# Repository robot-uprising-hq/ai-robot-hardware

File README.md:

# Micro Invaders - Hardware

This repository contains the hardware-related files of Robot Uprising Micro Invaders. The folder structure is as follows
* Root: Contains 3D printable basic robot parts
	* Accessories: Contains 3D printable accessories designed by Robot Uprising
	* Advanced: Contains design files
	* Images: Contains images mainly for README files
	* Misc: Contains miscellaneous 3D printable files related to the design, but not needed for the competition

The Micro Invaders robot is designed with simplicity in mind. It has very little amount of mechanical parts, and all the parts are 3D-printable. Moreover, it is designed to be assembled or disassembled without using any tools. 

If you need a 3D-printing guide, here is our guide: [3D-Printing Guide - Ultimaker 3](https://docs.google.com/document/d/1BAfrNYozn9PcpJIatZrwz-if5QTi_UQTAYi0SMTYilM/).

## Table of Contents <!-- omit in toc -->

- [Micro Invaders - Hardware](#micro-invaders---hardware)
	- [Mechanical parts](#mechanical-parts)
		- [Printing Checklist](#printing-checklist)
		- [Accesories](#accesories)
	- [Electronics](#electronics)
		- [Driver PCBA](#driver-pcba)
			- [PCB Gerber files and Bill of Materials](#pcb-gerber-files-and-bill-of-materials)
			- [PCBA Bill of Materials](#pcba-bill-of-materials)
		- [ESP32](#esp32)
		- [Motors](#motors)
		- [Batteries](#batteries)
		- [Cables and connectors](#cables-and-connectors)

## Mechanical parts

**Drive wheel:** This part drives the track, and the robot hence the name "drive wheel". The clearances are adjusted so that it fits nicely on the motor shaft, but it features a screw hole in case it doesn't.

**Idler:** This is the non-driving wheel for the tracks, but it also doubles as a tensioner. Thanks to its eccentric shaft, it can be used to adjust the slack on the chain.

**Idler retainer:** Idler retainer retains the idler :)

**Body:** This is the chassis of the robot. It houses all the parts. There are two versions of body. One is accessorizable and the other one is plain (located in Misc folder). As the name implies, accessorizable body is designed to fit accessories utilizing standard accessory connector.

**Top cover:** This part basically prevents things from falling off. It keeps the batteries in place, it prevents circuit board to fall off, and it even acts as the idler retainer retainer. All these functions in one single part. It attaches to the body by one rigid attachment point in the back, and one flexible attachment point in the front. This part also has two versions, accessorizable and plain (located in Misc folder).

**Track:** This is the part that moves the robot. It is basically a chain with 20 links.

### Printing Checklist

You will need to print the following parts for the competition.

| Amount | Part                       |
| :----: | -------------------------- |
|   1    | Body (accessorizable)      |
|   1    | Top cover (accessorizable) |
|   1    | Aruco marker holder        |
|   2    | Drive wheel                |
|   2    | Idler retainer             |
|   2    | Track                      |
|   2    | Idler                      |

See folders [Mechanics/Robot/STL](Mechanics/Robot/STL) and [Mechanics/Accessories/STL](Mechanics/Accessories/STL) for the STL-files for printing.

We recommend printing the parts in the given order as the latter parts are more advanced, and you might benefit from the experience. 
 
Also, feel free to design and print your own super exotic accessories or custom robot bodies for showing off between the matches, although you might not be allowed to use them in the competition. 

### Accesories

You can design and print your own front accessory as long as it complies with the [rules](https://github.com/robot-uprising-hq/ai-rules-mi2020).

## Electronics

### Driver PCBA

#### PCB Gerber files and Bill of Materials

You can find Gerber files for the PCB in the folder [Gerber Files](Electronics/Gerber%20Files). You can upload the compressed file to a PCB manufacturers website (e.g. JLCPCB)

Connect the right motor to J2 and the left motor to J3. Ensure motors have the correct polarity before fully assembling the robot to avoid unnecessary disassembly.

#### PCBA Bill of Materials

ID matches the schema and the PCB silkscreen

|         ID         | Description with link                                                                                                                                                                                              | Amount |
| :----------------: | ------------------------------------------------------------------------------------------------------------------------------------------------------------------------------------------------------------------ | :----: |
|       C1, C2       | [25V 100uF electrolytic THT capacitor](https://www.digikey.fi/en/products/detail/panasonic-electronic-components/ECA-1EM101B/268461)                                                                               |   2    |
|   D1, D2, D3, D4   | [RED clear 0805 SMD LED](https://www.digikey.fi/en/products/detail/liteon/LTST-C171KRKT/386801)                                                                                                                    |   4    |
|         F1         | [2.5A (Max Hold Current), 5A (Trip Current) 16V Fuse 2920 (7351 metric) package](https://www.digikey.fi/en/products/detail/bel-fuse-inc/0ZCF0250FF2C/4156185)                                                      |   1    |
|         J1         | [3-pin JST XH 2.50mm pitch connector](https://www.digikey.fi/en/products/detail/jst-sales-america-inc/S3B-XH-A/1651048)                                                                                            |   1    |
|       J2, J3       | [2-pin JST PH 2.00mm pitch connector](https://www.digikey.fi/fi/products/detail/jst-sales-america-inc/S2B-PH-SM4-TB/926655?s=N4IgTCBcDaIMpgEIFoAKAJZcCyAWZAKoiALoC%2BQA)                                           |   2    |
| R1, R2, R3, R4, R6 | [1 kΩ 0805 SMD resistor](https://www.digikey.fi/en/products/detail/stackpole-electronics-inc/RMCF0805JT1K00/1757881)                                                                                               |   5    |
|         R5         | [2.2 kΩ 0805 SMD resistor](https://www.digikey.fi/en/products/detail/stackpole-electronics-inc/RMCF0805JT2K20/1757894)                                                                                             |   1    |
|        SW1         | [Slide switch](https://www.digikey.fi/en/products/detail/c-k/OS102011MA1QN1/1981430)                                                                                                                               |   1    |
|         U1         | [7805 5V linear regulator (D2PAK Package)](https://www.digikey.fi/en/products/detail/onsemi/MC7805CD2TR4G/919332)                                                                                                  |   1    |
|    U2 (J4, J5)     | [For ESP-32 two 20-pin 2.54mm pitch female headers which needs to be trimmed to 19 pins](https://www.digikey.fi/fi/products/detail/w%C3%BCrth-elektronik/61302011821/16608603?s=N4IgTCBcDaIGwEYDMAGMKEIBxgSAugL5A) |   2    |
|         U3         | [Dual H-bridge motor driver 293D](https://www.digikey.fi/en/products/detail/stmicroelectronics/L293D/634700)                                                                                                       |   1    |

### ESP32

ESP32-DEVKITC-32E:

- 1 x https://www.digikey.fi/en/products/detail/espressif-systems/ESP32-DEVKITC-32E/12091810

### Motors

Olimex LTD: MG-6-48

- 2 x https://www.digikey.fi/en/products/detail/olimex-ltd/MG-6-48/21662315

### Batteries

Two 18650 Li-Ion batteries (we recommend >2200mAh, with protection circuit):

- 2 x https://akkula.fi/tuote/xtar-18650-li-ion-akku-2600-mah-36v-suojapiiri-button-top/

Li-Ion 18650 battery charger:

- 1 x https://akkula.fi/tuote/xtar-mc2-plus-usb-pikalaturi-kahdelle-li-ion-akulle/

18650 battery holder for two batteries:

- 1 x https://akkula.fi/tuote/2-x-18650-asennuskotelo-johdoilla-max-1-a-virta/

### Cables and connectors

We recommend getting JST XH (2.50mm pitch) and PH (2.00mm pitch) connector assortment with crimp tool.
The JST connectors require crimping the cable ends with a tool such as https://www.partco.fi/fi/tyoekalut/puristuspihdit/loput-puristuspihdit/11353-ht213.html. 
Unless you're very much into crimping all the things, instead of buying the tool you can probably find one at your local university electronics lab, makerspace or https://hacklab.fi.

There are also preassembed wires: (we recommend 12" ones so that they are long enough)

XH:
https://www.digikey.fi/en/products/filter/jumper-wires-pre-crimped-leads/453?s=N4IgTCBcDaIFYGcAuACAHgCxAXQL5A

12" ones:
https://www.digikey.fi/en/products/detail/jst-sales-america-inc/ASXHSXH22K305/6684932

PH:
https://www.digikey.fi/en/products/filter/jumper-wires-pre-crimped-leads/453?s=N4IgTCBcDaIFYGcAuACADgCxAXQL5A

12" ones:
https://www.digikey.fi/en/products/detail/jst-sales-america-inc/ASPHSPH24K305/6009459

3-pin JST XH 2.50mm pitch Connector for battery terminal:
- Female 1 x https://www.digikey.fi/fi/products/detail/jst-sales-america-inc/XHP-2/555485

2-pin JST PH 2.00mm pitch Connector for motor terminals:
- Female 2 x https://www.digikey.fi/en/products/detail/jst-sales-america-inc/PHR-2/608607

### Firmware

There are two firmware repositories for this robot.
- Control the robot using a computer: [github.com/robot-uprising-hq/ai-robot-udp](https://github.com/robot-uprising-hq/ai-robot-udp)
	- Official firmware for receiving commands over WIFI (using UDP) and limited support for bluetooth
- Control the robot using a gamepad: [github.com/zero-ones-given/bluetooth-gamepad-robot-firmware](https://github.com/zero-ones-given/bluetooth-gamepad-robot-firmware)
	- Community built firmware for controlling the robot over bluetooth with a gamepad

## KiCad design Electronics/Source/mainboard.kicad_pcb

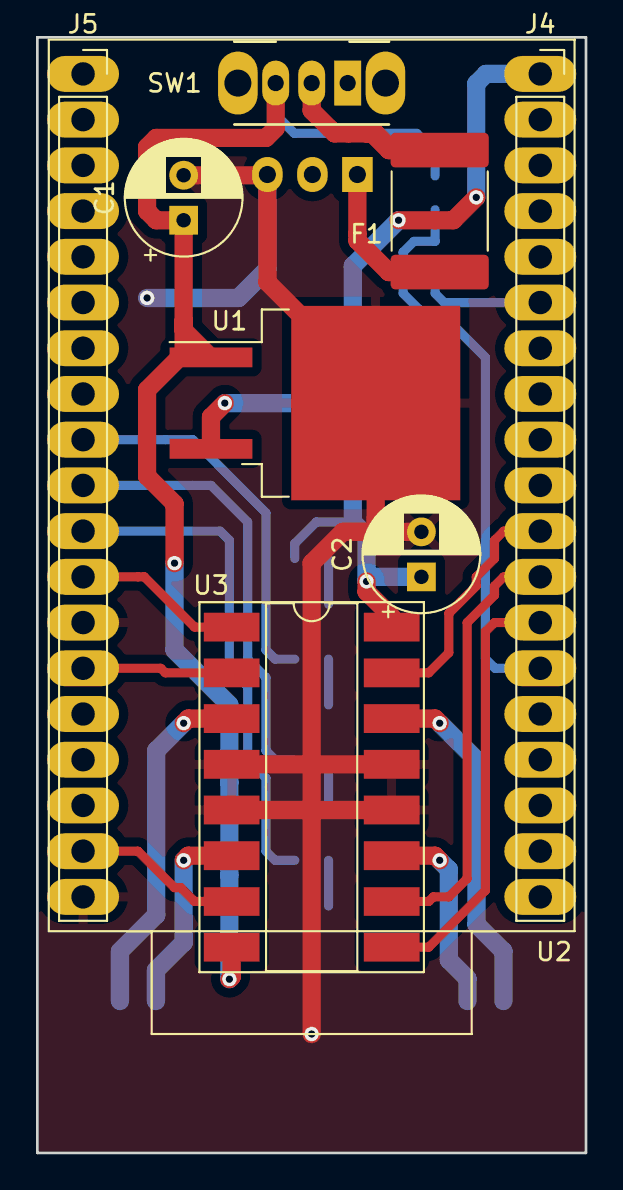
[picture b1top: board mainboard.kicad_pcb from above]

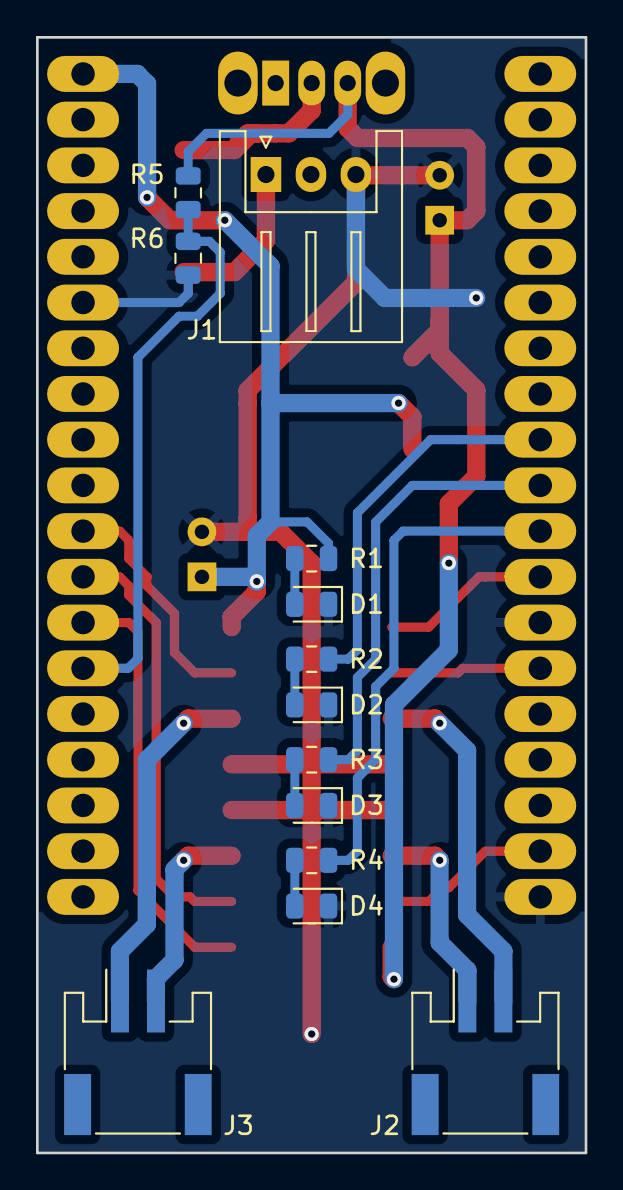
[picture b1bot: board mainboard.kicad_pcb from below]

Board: 2 copper layers, 30.5 x 62.0 mm, 22 parts (13 on the bottom side), 23 nets.

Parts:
C1, C2: 100uF; CP_Radial_D6.3mm_P2.50mm
D1, D2, D3, D4: LED; LED_0805_2012Metric
F1: b0250 2.5A; Fuse_2920_7451Metric
J1: Conn_01x03; JST_XH_S03B-XH-A_1x03_P2.50mm_Horizontal
J2, J3: Conn_01x02; JST_PH_S2B-PH-SM4-TB_1x02-1MP_P2.00mm_Horizontal
J4, J5: Conn_01x19_Socket; PinSocket_1x19_P2.54mm_Vertical
R1, R2, R3, R4: 330 ohm; R_0805_2012Metric
R5: 2.2k; R_0805_2012Metric
R6: 1k; R_0805_2012Metric
SW1: SW_DPDT_x2; SW_CuK_OS102011MA1QN1_SPDT_Angled
U1: L7805; TO-263-2
U2: ESP32-DEVKITC
U3: L293; DIP-16_W8.89mm_SMDSocket_LongPads

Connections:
/5V: C2.1, J4.1, R1.1, U1.3 (OUT), U2.19 (5V), U3.16 (VCC1)
/ACTIVITY_LED: J5.11, R4.2, U2.30 (IO18)
/GND: C1.2, C2.2, D1.1 (K), D2.1 (K), D3.1 (K), D4.1 (K), J1.3, J4.6, J5.13, J5.19, R6.2, U1.2 (GND), U2.14 (GND), U2.32 (GND), U2.38 (GND), U3.4 (GND), U3.5 (GND), U3.12 (GND), U3.13 (GND)
/HV: C1.1, R5.1, SW1.3 (C), U1.1 (IN), U3.8 (VCC2)
/MOT_1_DIR_A: J5.14, U2.33 (IO21), U3.2 (1A)
/MOT_1_DIR_B: J5.18, U2.37 (IO23), U3.7 (2A)
/MOT_1_NEG: J2.2, U3.3 (1Y)
/MOT_1_POS: J2.1, U3.6 (2Y)
/MOT_2_DIR_A: J4.12, U2.8 (IO33), U3.10 (3A)
/MOT_2_DIR_B: J4.11, U2.9 (IO25), U3.15 (4A)
/MOT_2_NEG: J3.2, U3.11 (3A)
/MOT_2_POS: J3.1, U3.14 (4Y)
/PWM_1: J5.12, U2.31 (IO19), U3.1 (EN1,2)
/PWM_2: J4.13, U2.7 (IO32), U3.9 (EN3,4)
/SERVER_LED: J5.10, R3.2, U2.29 (IO5)
/V_BATT: F1.2, J1.1
/V_SENSE: J4.14, R5.2, R6.1, U2.6 (IO35)
/WIFI_LED: J5.9, R2.2, U2.28 (IO17)
unnamed: D1.2 (A), R1.2
unnamed: D2.2 (A), R2.1
unnamed: D3.2 (A), R3.1
unnamed: D4.2 (A), R4.1
unnamed: F1.1, SW1.2 (B)

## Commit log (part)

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2020-09-27 Robot STLs added, some accessories added
2020-09-27 CAD files added for the robot & electronics
2020-09-29 Templates for readme added
2020-09-29 Readme for the general robot
2020-09-29 Formatting
2020-09-29 Parts descriptions added
2020-09-29 Printing checklist added
2020-09-29 Minor printing order change
2020-09-29 Add a link to 3D-printing guide
    Also changes the order of some sentences.
2020-10-25 Bumps on the arena added
2021-05-16 Motor cable strain relief added
2024-04-15 Added Gerber files and BOM
2024-04-15 Added more parts with links
2024-04-15 Edited cables and connector BOM
2024-04-15 More fixes
2024-04-15 And more fixes
2024-04-15 more.... fixes...
2024-04-15 updated KiCad project
2024-04-15 Edited README
2024-04-15 cleaned up v2 KiCAD project files
2025-04-12 resturcturing
2025-04-12 STL transfers and kicad cleanup
2025-04-12 Readme corrections
2025-04-12 Clean
2025-04-14 renaming and readme improvements
2025-04-14 Remove erronously added file
2025-04-14 3D file cleanup
2025-04-25 v1.1.1
    Restructured folders
2026-02-24 Improve README.md
    Add links to firmware repositories and some folders within this repo. Add mention of which sides the motors should go on.
